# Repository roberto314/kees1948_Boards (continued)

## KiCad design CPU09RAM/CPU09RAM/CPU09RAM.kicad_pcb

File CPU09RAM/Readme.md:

# kees1948_Boards
kees 1948 Uniflex Ram Board Remake

This is my recreation of the Uniflex RAM Board. It includes two CR2032 Batteries and a MXD1210 RAM Controller. It is mainly SMD.

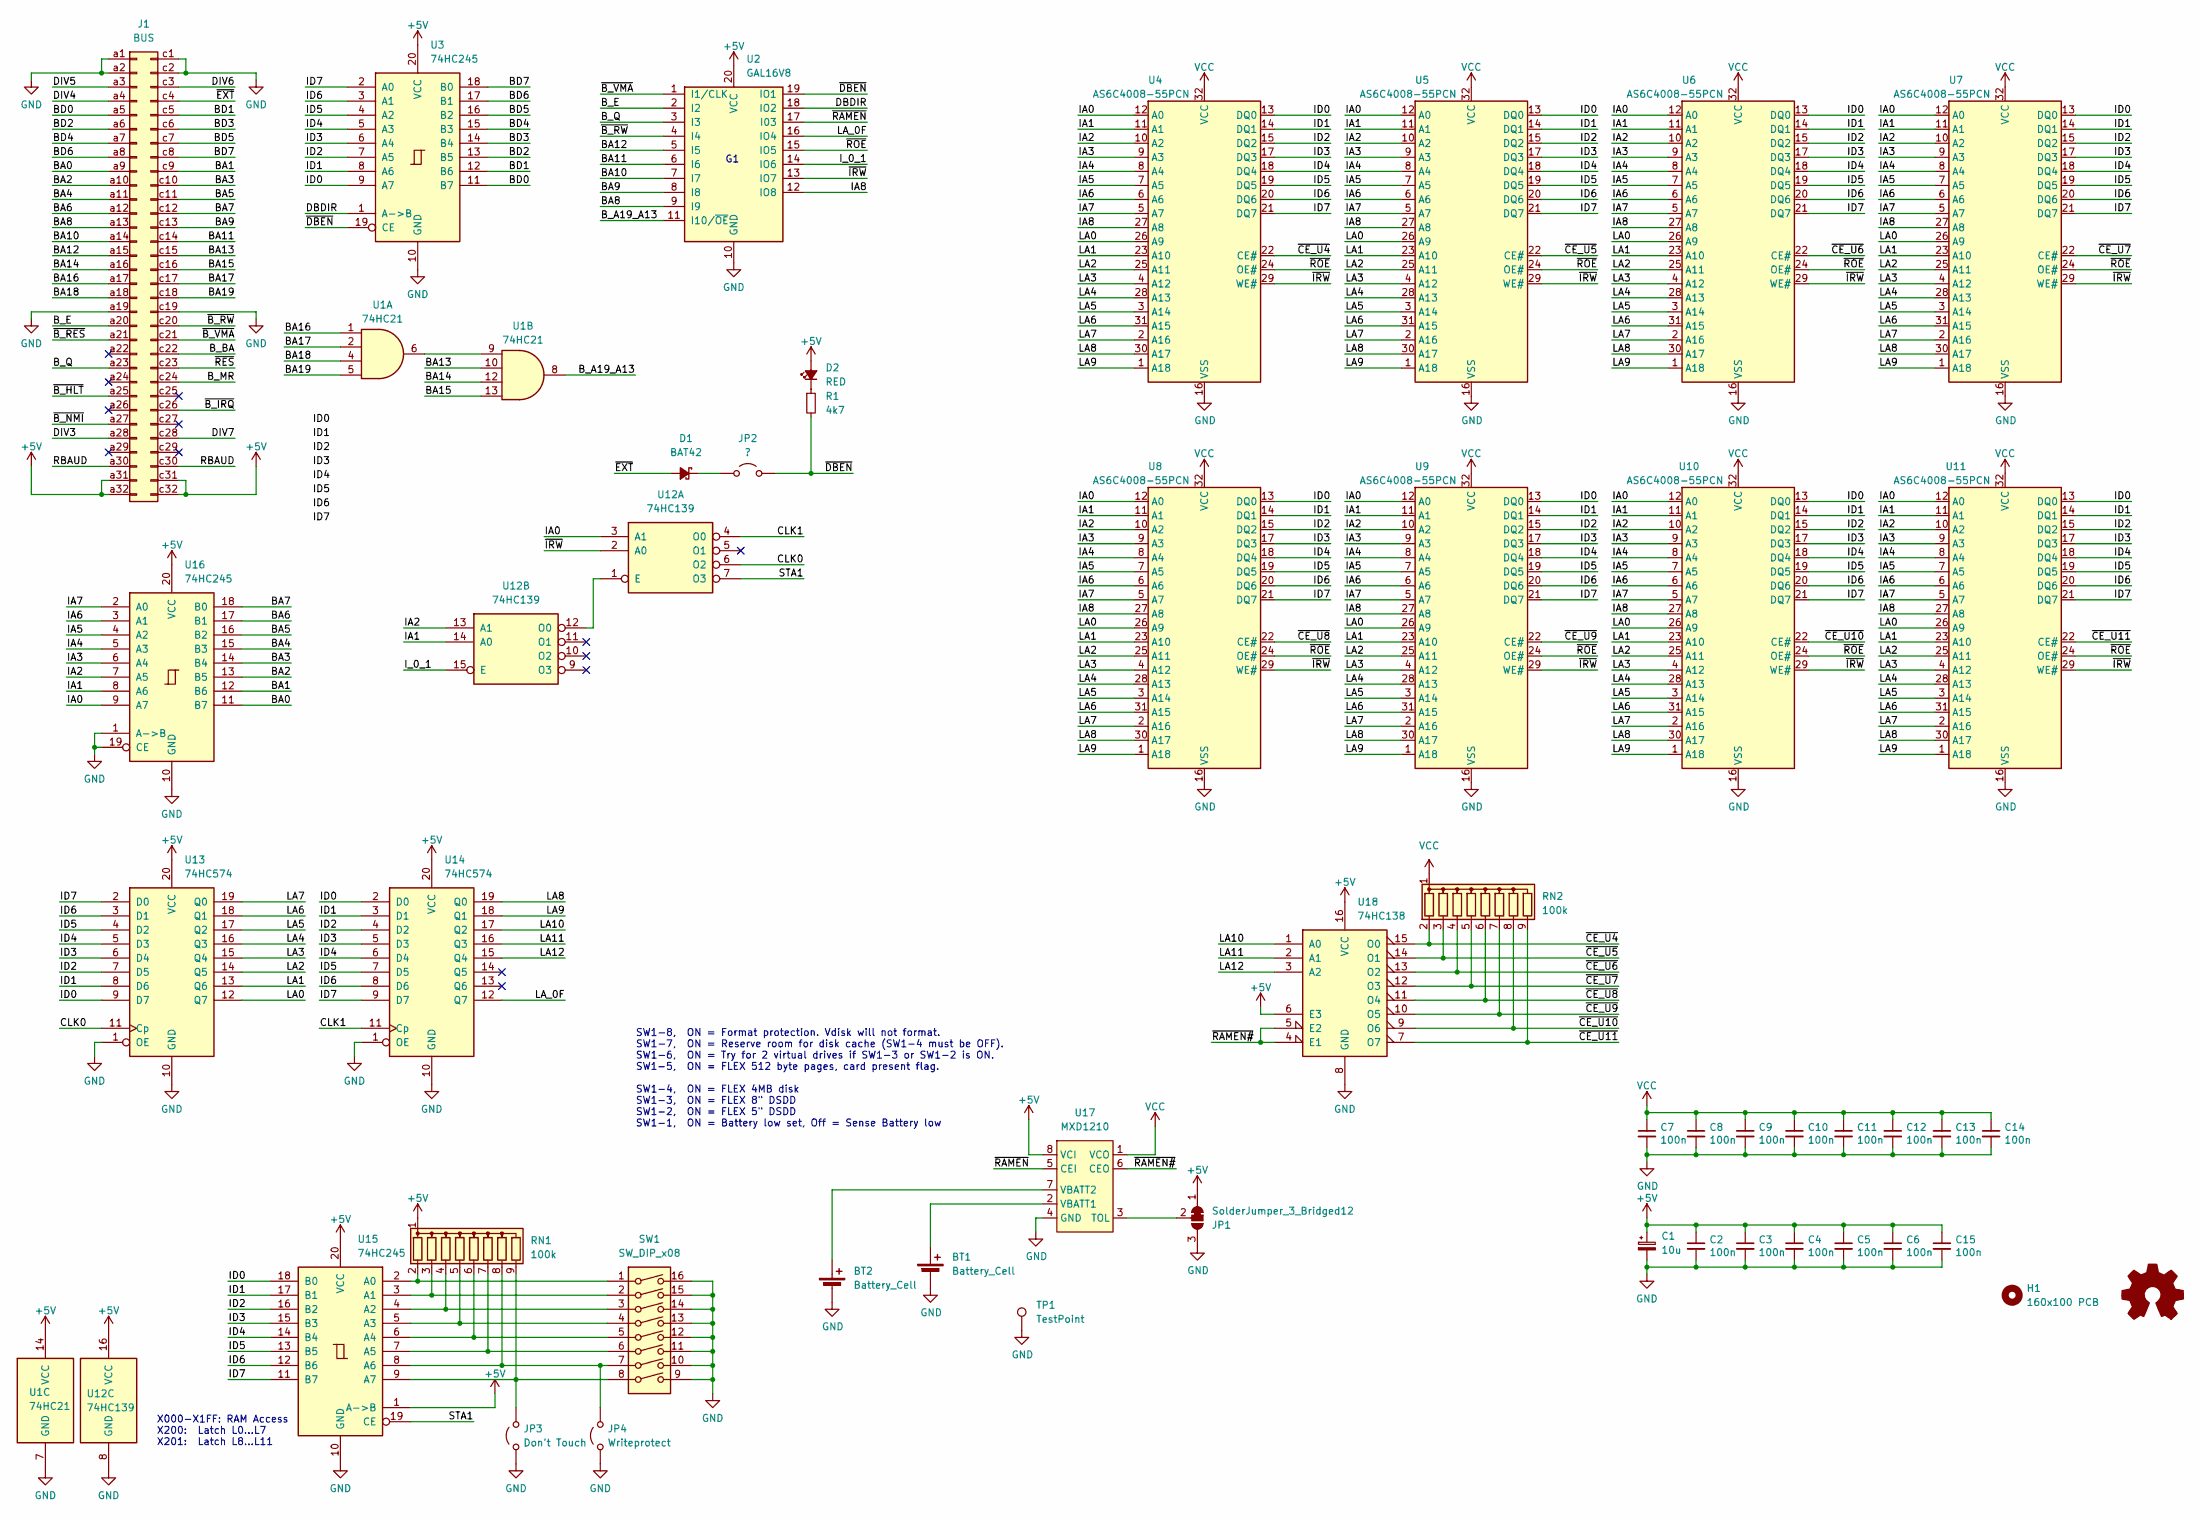
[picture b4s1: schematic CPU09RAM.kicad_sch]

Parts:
BT1, BT2: Battery_Cell; BatteryHolder_Keystone_3002_1x2032
C1: 10u; CP_EIA-7343-31_Kemet-D_Pad2.25x2.55mm_HandSolder
C2, C3, C4, C5, C6, C7, C8, C9, C10, C11, C12, C13, C14, C15: 100n; C_1206_3216Metric_Pad1.33x1.80mm_HandSolder
D1: BAT42; D_DO-15_P10.16mm_Horizontal
D2: RED; LED_D3.0mm
H1: 160x100 PCB; Eurocard_160x100_19inch_holes_connector
J1: BUS; DIN41612_C_2x32_Male_Horizontal_THT
JP1: SolderJumper_3_Bridged12; SolderJumper-3_P1.3mm_Bridged12_RoundedPad1.0x1.5mm
JP2: ?; PinHeader_1x02_P2.54mm_Vertical
JP3: Don't Touch; PinHeader_1x02_P2.54mm_Vertical
JP4: Writeprotect; PinHeader_1x02_P2.54mm_Vertical
R1: 4k7; R_1206_3216Metric_Pad1.30x1.75mm_HandSolder
RN1, RN2: 100k; R_Array_SIP9
SW1: SW_DIP_x08; DIP-16_W7.62mm_Socket
TP1: TestPoint; TestPoint_Keystone_5005-5009_Compact
U1: 74HC21; SO-14_3.9x8.65mm_P1.27mm
U2: GAL16V8; DIP-20_W7.62mm_Socket
U3: 74HC245; SOIC-20W_7.5x12.8mm_P1.27mm
U4, U5, U6, U7, U8, U9, U10, U11: AS6C4008-55PCN; SOP-32_11.305x20.495mm_P1.27mm
U12: 74HC139; SOIC-16_3.9x9.9mm_P1.27mm
U13, U14: 74HC574; SOP-20_7.5x12.8mm_P1.27mm
U15, U16: 74HC245; SOP-20_7.5x12.8mm_P1.27mm
U17: MXD1210; SOIC-8_3.9x4.9mm_P1.27mm
U18: 74HC138; SOIC-16_3.9x9.9mm_P1.27mm

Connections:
+5V: C1.1, C2.1, C3.1, C4.1, C5.1, C6.1, C15.1, D2.2 (A), J1.a31, J1.a32, J1.c31, J1.c32, JP1.1 (A), RN1.1 (common), U1.14 (VCC), U2.20 (VCC), U3.20 (VCC), U12.16 (VCC), U13.20 (VCC), U14.20 (VCC), U15.1 (A->B), U15.20 (VCC), U16.20 (VCC), U17.8 (VCI), U18.6 (E3), U18.16 (VCC)
/BA0: J1.a9, U16.11 (B7)
/BA1: J1.c9, U16.12 (B6)
/BA2: J1.a10, U16.13 (B5)
/BA3: J1.c10, U16.14 (B4)
/BA4: J1.a11, U16.15 (B3)
/BA5: J1.c11, U16.16 (B2)
/BA6: J1.a12, U16.17 (B1)
/BA7: J1.c12, U16.18 (B0)
/BA8: J1.a13, U2.9 (I9)
/BA9: J1.c13, U2.8 (I8)
/BA10: J1.a14, U2.7 (I7)
/BA11: J1.c14, U2.6 (I6)
/BA12: J1.a15, U2.5 (I5)
/BA13: J1.c15, U1.10
/BA14: J1.a16, U1.12
/BA15: J1.c16, U1.13
/BA16: J1.a17, U1.1
/BA17: J1.c17, U1.2
/BA18: J1.a18, U1.4
/BA19: J1.c18, U1.5
/BD0: J1.a5, U3.11 (B7)
/BD1: J1.c5, U3.12 (B6)
/BD2: J1.a6, U3.13 (B5)
/BD3: J1.c6, U3.14 (B4)
/BD4: J1.a7, U3.15 (B3)
/BD5: J1.c7, U3.16 (B2)
/BD6: J1.a8, U3.17 (B1)
/BD7: J1.c8, U3.18 (B0)
/B_A19_A13: U1.8, U2.11 (I10/~OE)
/B_BA: J1.c22
/B_E: J1.a20, U2.2 (I2)
/B_MR: J1.c24
/B_Q: J1.a23, U2.3 (I3)
/CLK0: U12.6 (O2), U13.11 (Cp)
/CLK1: U12.4 (O0), U14.11 (Cp)
/DBDIR: U2.18 (IO2), U3.1 (A->B)
/DIV3: J1.a28
/DIV4: J1.a4
/DIV5: J1.a3
/DIV6: J1.c3
/DIV7: J1.c28
/IA0: U4.12 (A0), U5.12 (A0), U6.12 (A0), U7.12 (A0), U8.12 (A0), U9.12 (A0), U10.12 (A0), U11.12 (A0), U12.3 (A1), U16.9 (A7)
/IA1: U4.11 (A1), U5.11 (A1), U6.11 (A1), U7.11 (A1), U8.11 (A1), U9.11 (A1), U10.11 (A1), U11.11 (A1), U12.14 (A0), U16.8 (A6)
/IA2: U4.10 (A2), U5.10 (A2), U6.10 (A2), U7.10 (A2), U8.10 (A2), U9.10 (A2), U10.10 (A2), U11.10 (A2), U12.13 (A1), U16.7 (A5)
/IA3: U4.9 (A3), U5.9 (A3), U6.9 (A3), U7.9 (A3), U8.9 (A3), U9.9 (A3), U10.9 (A3), U11.9 (A3), U16.6 (A4)
/IA4: U4.8 (A4), U5.8 (A4), U6.8 (A4), U7.8 (A4), U8.8 (A4), U9.8 (A4), U10.8 (A4), U11.8 (A4), U16.5 (A3)
/IA5: U4.7 (A5), U5.7 (A5), U6.7 (A5), U7.7 (A5), U8.7 (A5), U9.7 (A5), U10.7 (A5), U11.7 (A5), U16.4 (A2)
/IA6: U4.6 (A6), U5.6 (A6), U6.6 (A6), U7.6 (A6), U8.6 (A6), U9.6 (A6), U10.6 (A6), U11.6 (A6), U16.3 (A1)
/IA7: U4.5 (A7), U5.5 (A7), U6.5 (A7), U7.5 (A7), U8.5 (A7), U9.5 (A7), U10.5 (A7), U11.5 (A7), U16.2 (A0)
/IA8: U2.12 (IO8), U4.27 (A8), U5.27 (A8), U6.27 (A8), U7.27 (A8), U8.27 (A8), U9.27 (A8), U10.27 (A8), U11.27 (A8)
/ID0: U3.9 (A7), U4.13 (DQ0), U5.13 (DQ0), U6.13 (DQ0), U7.13 (DQ0), U8.13 (DQ0), U9.13 (DQ0), U10.13 (DQ0), U11.13 (DQ0), U13.9 (D7), U14.2 (D0), U15.18 (B0)
/ID1: U3.8 (A6), U4.14 (DQ1), U5.14 (DQ1), U6.14 (DQ1), U7.14 (DQ1), U8.14 (DQ1), U9.14 (DQ1), U10.14 (DQ1), U11.14 (DQ1), U13.8 (D6), U14.3 (D1), U15.17 (B1)
/ID2: U3.7 (A5), U4.15 (DQ2), U5.15 (DQ2), U6.15 (DQ2), U7.15 (DQ2), U8.15 (DQ2), U9.15 (DQ2), U10.15 (DQ2), U11.15 (DQ2), U13.7 (D5), U14.4 (D2), U15.16 (B2)
/ID3: U3.6 (A4), U4.17 (DQ3), U5.17 (DQ3), U6.17 (DQ3), U7.17 (DQ3), U8.17 (DQ3), U9.17 (DQ3), U10.17 (DQ3), U11.17 (DQ3), U13.6 (D4), U14.5 (D3), U15.15 (B3)
/ID4: U3.5 (A3), U4.18 (DQ4), U5.18 (DQ4), U6.18 (DQ4), U7.18 (DQ4), U8.18 (DQ4), U9.18 (DQ4), U10.18 (DQ4), U11.18 (DQ4), U13.5 (D3), U14.6 (D4), U15.14 (B4)
/ID5: U3.4 (A2), U4.19 (DQ5), U5.19 (DQ5), U6.19 (DQ5), U7.19 (DQ5), U8.19 (DQ5), U9.19 (DQ5), U10.19 (DQ5), U11.19 (DQ5), U13.4 (D2), U14.7 (D5), U15.13 (B5)
/ID6: U3.3 (A1), U4.20 (DQ6), U5.20 (DQ6), U6.20 (DQ6), U7.20 (DQ6), U8.20 (DQ6), U9.20 (DQ6), U10.20 (DQ6), U11.20 (DQ6), U13.3 (D1), U14.8 (D6), U15.12 (B6)
/ID7: U3.2 (A0), U4.21 (DQ7), U5.21 (DQ7), U6.21 (DQ7), U7.21 (DQ7), U8.21 (DQ7), U9.21 (DQ7), U10.21 (DQ7), U11.21 (DQ7), U13.2 (D0), U14.9 (D7), U15.11 (B7)
/I_0_1: U2.14 (IO6), U12.15 (E)
/LA0: U4.26 (A9), U5.26 (A9), U6.26 (A9), U7.26 (A9), U8.26 (A9), U9.26 (A9), U10.26 (A9), U11.26 (A9), U13.12 (Q7)
/LA1: U4.23 (A10), U5.23 (A10), U6.23 (A10), U7.23 (A10), U8.23 (A10), U9.23 (A10), U10.23 (A10), U11.23 (A10), U13.13 (Q6)
/LA2: U4.25 (A11), U5.25 (A11), U6.25 (A11), U7.25 (A11), U8.25 (A11), U9.25 (A11), U10.25 (A11), U11.25 (A11), U13.14 (Q5)
/LA3: U4.4 (A12), U5.4 (A12), U6.4 (A12), U7.4 (A12), U8.4 (A12), U9.4 (A12), U10.4 (A12), U11.4 (A12), U13.15 (Q4)
/LA4: U4.28 (A13), U5.28 (A13), U6.28 (A13), U7.28 (A13), U8.28 (A13), U9.28 (A13), U10.28 (A13), U11.28 (A13), U13.16 (Q3)
/LA5: U4.3 (A14), U5.3 (A14), U6.3 (A14), U7.3 (A14), U8.3 (A14), U9.3 (A14), U10.3 (A14), U11.3 (A14), U13.17 (Q2)
/LA6: U4.31 (A15), U5.31 (A15), U6.31 (A15), U7.31 (A15), U8.31 (A15), U9.31 (A15), U10.31 (A15), U11.31 (A15), U13.18 (Q1)
/LA7: U4.2 (A16), U5.2 (A16), U6.2 (A16), U7.2 (A16), U8.2 (A16), U9.2 (A16), U10.2 (A16), U11.2 (A16), U13.19 (Q0)
/LA8: U4.30 (A17), U5.30 (A17), U6.30 (A17), U7.30 (A17), U8.30 (A17), U9.30 (A17), U10.30 (A17), U11.30 (A17), U14.19 (Q0)
/LA9: U4.1 (A18), U5.1 (A18), U6.1 (A18), U7.1 (A18), U8.1 (A18), U9.1 (A18), U10.1 (A18), U11.1 (A18), U14.18 (Q1)
/LA10: U14.17 (Q2), U18.1 (A0)
/LA11: U14.16 (Q3), U18.2 (A1)
/LA12: U14.15 (Q4), U18.3 (A2)
/LA_0F: U2.16 (IO4), U14.12 (Q7)
/RBAUD: J1.a30, J1.c30
/STA1: U12.7 (O3), U15.19 (CE)
/~B_HLT: J1.a25
/~B_IRQ: J1.c26
/~B_NMI: J1.a27
/~B_RES: J1.a21
/~B_RW: J1.c20, U2.4 (I4)
/~B_VMA: J1.c21, U2.1 (I1/CLK)
/~CE_U4: RN2.2 (R1), U4.22 (CE#), U18.15 (O0)
/~CE_U5: RN2.3 (R2), U5.22 (CE#), U18.14 (O1)
/~CE_U6: RN2.4 (R3), U6.22 (CE#), U18.13 (O2)
/~CE_U7: RN2.5 (R4), U7.22 (CE#), U18.12 (O3)
/~CE_U8: RN2.6 (R5), U8.22 (CE#), U18.11 (O4)
/~CE_U9: RN2.7 (R6), U9.22 (CE#), U18.10 (O5)
/~CE_U10: RN2.8 (R7), U10.22 (CE#), U18.9 (O6)
/~CE_U11: RN2.9 (R8), U11.22 (CE#), U18.7 (O7)
/~DBEN: JP2.2 (B), R1.2, U2.19 (IO1), U3.19 (CE)
/~EXT: D1.2 (A), J1.c4
/~IRW: U2.13 (IO7), U4.29 (WE#), U5.29 (WE#), U6.29 (WE#), U7.29 (WE#), U8.29 (WE#), U9.29 (WE#), U10.29 (WE#), U11.29 (WE#), U12.2 (A0)
/~RAMEN#: U17.6 (CEO), U18.4 (E1), U18.5 (E2)
/~RAMEN: U2.17 (I03), U17.5 (CEI)
/~RES: J1.c23
/~ROE: U2.15 (IO5), U4.24 (OE#), U5.24 (OE#), U6.24 (OE#), U7.24 (OE#), U8.24 (OE#), U9.24 (OE#), U10.24 (OE#), U11.24 (OE#)
GND: BT1.2 (-), BT2.2 (-), C1.2, C2.2, C3.2, C4.2, C5.2, C6.2, C7.2, C8.2, C9.2, C10.2, C11.2, C12.2, C13.2, C14.2, C15.2, J1.a1, J1.a2, J1.a19, J1.c1, J1.c2, J1.c19, JP1.3 (B), JP3.1 (A), JP4.1 (A), SW1.9, SW1.10, SW1.11, SW1.12, SW1.13, SW1.14, SW1.15, SW1.16, TP1.1, U1.7 (GND), U2.10 (GND), U3.10 (GND), U4.16 (VSS), U5.16 (VSS), U6.16 (VSS), U7.16 (VSS), U8.16 (VSS), U9.16 (VSS), U10.16 (VSS), U11.16 (VSS), U12.8 (GND), U13.1 (OE), U13.10 (GND), U14.1 (OE), U14.10 (GND), U15.10 (GND), U16.1 (A->B), U16.10 (GND), U16.19 (CE), U17.4 (GND), U18.8 (GND)
unnamed: BT1.1 (+), U17.2 (VBATT1)
unnamed: BT2.1 (+), U17.7 (VBATT2)
unnamed: D1.1 (K), JP2.1 (A)
unnamed: D2.1 (K), R1.1
unnamed: JP1.2 (C), U17.3 (TOL)
unnamed: JP3.2 (B), RN1.9 (R8), SW1.8, U15.9 (A7)
unnamed: JP4.2 (B), RN1.8 (R7), SW1.7, U15.8 (A6)
unnamed: RN1.2 (R1), SW1.1, U15.2 (A0)
unnamed: RN1.3 (R2), SW1.2, U15.3 (A1)
unnamed: RN1.4 (R3), SW1.3, U15.4 (A2)
unnamed: RN1.5 (R4), SW1.4, U15.5 (A3)
unnamed: RN1.6 (R5), SW1.5, U15.6 (A4)
unnamed: RN1.7 (R6), SW1.6, U15.7 (A5)
unnamed: U1.6, U1.9
unnamed: U12.1 (E), U12.12 (O0)
VCC: C7.1, C8.1, C9.1, C10.1, C11.1, C12.1, C13.1, C14.1, RN2.1 (common), U4.32 (VCC), U5.32 (VCC), U6.32 (VCC), U7.32 (VCC), U8.32 (VCC), U9.32 (VCC), U10.32 (VCC), U11.32 (VCC), U17.1 (VCO)

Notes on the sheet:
SW1-8, ON = Format protection. Vdisk will not format. SW1-7, ON = Reserve room for disk cache (SW1-4 must be OFF). SW1-6, ON = Try for 2 virtual drives if SW1-3 or SW1-2 is ON. SW1-5, ON = FLEX 512 byte pages, card present flag. SW1-4, ON = FLEX 4MB disk SW1-3, ON = FLEX 8" DSDD SW1-2, ON = FLEX 5"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
X000-X1FF: RAM Access X200: Latch L0...L7 X201: Latch L8...L11

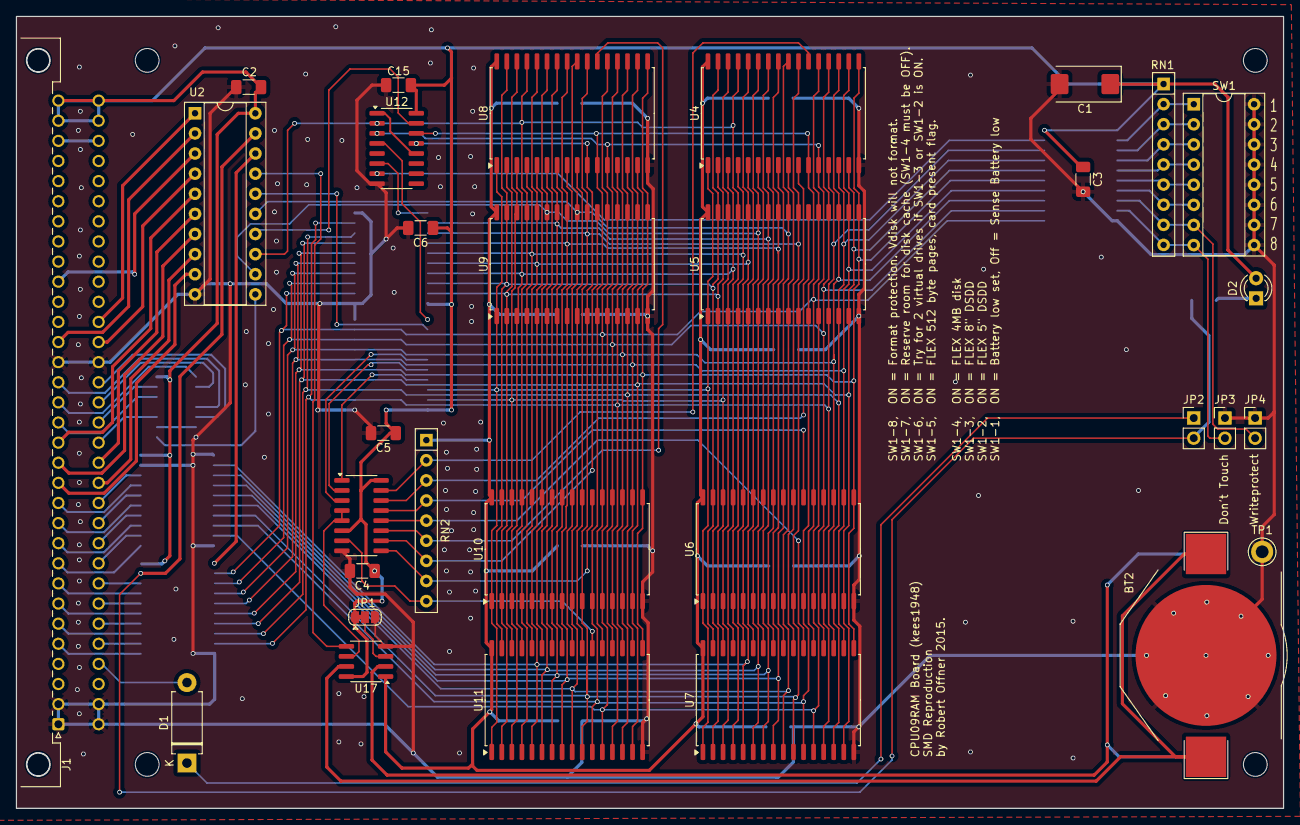
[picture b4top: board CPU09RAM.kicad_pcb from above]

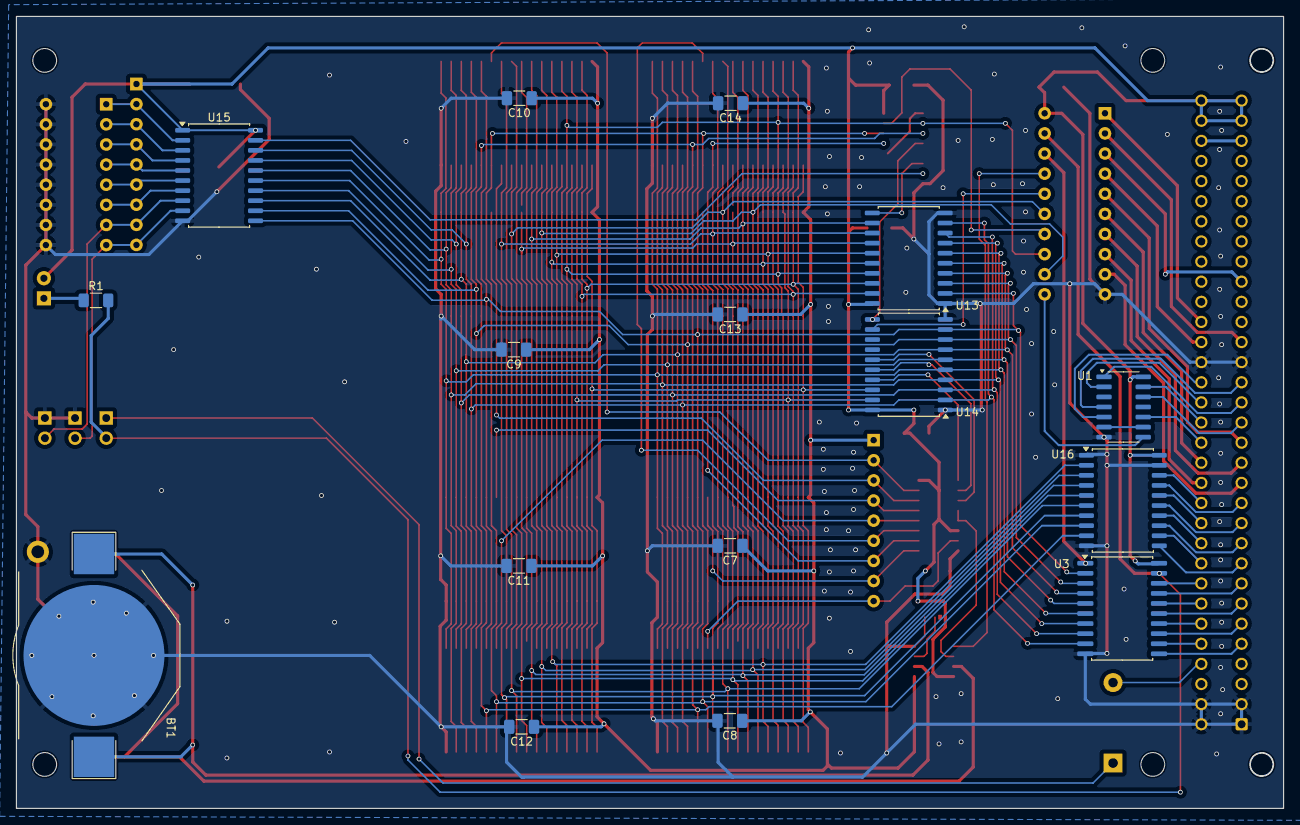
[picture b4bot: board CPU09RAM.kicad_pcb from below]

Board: 2 copper layers, 160.0 x 100.0 mm, 48 parts (16 on the bottom side), 102 nets.

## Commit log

2025-05-15 new repository
2025-05-17 FLP schematic ch.
2025-05-17 IDE schematic title ch.
2025-05-19 09NET added, 09FLP minor ch.
2025-05-20 Documentation upgrade
2025-05-20 kicad backup deleted
2025-06-21 Exorciser Doku added
2025-06-30 Backplane BP7 started with board
2025-06-30 Backplane BP7 mostly finished
2025-06-30 Backplane BP8 added
2025-08-22 new CPU09US4 Board added
2025-09-01 Exorset Floppy added
2025-09-09 Exordisk first version
2025-09-12 Board finished, GALS added
2025-09-12 Backups deleted
2025-09-12 Gerber new
2025-09-15 some small adjustments
2025-12-25 Exorset Floppy update
2025-12-25 pictures update
2025-12-30 first test with exordisk board, GALs new
2025-12-30 exordisk pic added
2025-12-30 Exordisk GAL G1 modified
2026-01-05 exordisk schematic updated, first working version
2026-01-06 new schematic for exordisk
2026-01-08 new GAL eq. for additional EPROM on board
2026-01-08 74LS73 ch. to LS112
2026-01-08 build script new
2026-01-09 floppy2 more comments
2026-01-11 more comments
2026-01-14 tried some stuff
2026-01-15 Readme update
2026-01-22 new build w. exbug11
2026-01-25 new build for extra drives
2026-01-27 first working version with three drives
2026-01-28 ch. the Exordisk portion to include all changes, Diagnostic and Printer moved to external ROM @ ED00
2026-02-02 some cleanup
2026-02-02 chasing bugs floppy2.asm
2026-02-03 nearly working for four drives
2026-02-05 work on floppy2.asm, four drives seem to work
2026-02-09 cleanup
2026-02-09 still working on floppy2.asm
2026-02-09 bug found in floppy2.asm no data was written
2026-02-18 first double sided format works
2026-02-18 more commens in floppy.asm
2026-02-19 Exordisk Board continued
2026-02-20 exordisk firmwar continued
2026-02-20 exordisk firmware first working for DS
2026-02-22 trying to get double side working
2026-02-22 more comments in floppy
2026-02-23 more comments in format
2026-02-24 exorsim added
2026-02-25 dual side works with gotek but not with real floppy
